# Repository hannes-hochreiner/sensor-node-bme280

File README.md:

# Sensor node BME280

A breakout board for the sensor node core featuring the BME280.

## Main parts

### BME280
  * Bosch Sensortec: BME280
  * Digi-Key: [828-1063-1-ND](https://www.digikey.de/product-detail/en/bosch-sensortec/BME280/828-1063-1-ND/6136314)
  * [Datasheet](https://ae-bst.resource.bosch.com/media/_tech/media/datasheets/BST-BME280-DS002.pdf)
  * [Driver](https://github.com/BoschSensortec/BME280_driver)
  * Price: 6.61

### Connector
  * Sullins Connector Solutions: GRPB052VWVN-RC
  * Digi-Key: [S9015E-05-ND](https://www.digikey.de/product-detail/en/sullins-connector-solutions/GRPB052VWVN-RC/S9015E-05-ND/1786455)
  * [Datasheet](https://media.digikey.com/pdf/Data%20Sheets/Sullins%20PDFs/GRPB_%20_2VWVN-RC%2010954-C.pdf)
  * Price: 0.63

## Price

estimate: 10 EUR

## Size

11 mm x 13 mm (connector 2.25 mm in)

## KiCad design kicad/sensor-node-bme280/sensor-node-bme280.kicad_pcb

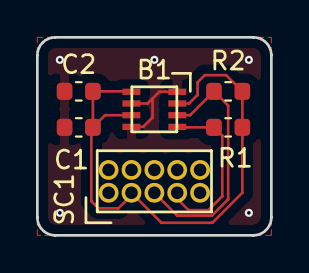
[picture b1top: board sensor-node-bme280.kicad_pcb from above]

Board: 2 copper layers, 13.0 x 11.0 mm, 6 parts (0 on the bottom side), 4 nets.

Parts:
B1: BME280; BME280_handsolder
C1, C2: 0.1µF; C_0603_1608Metric
R1, R2: 10k; R_0603_1608Metric
SC1: Sensor-Connector; sensor-connector-male

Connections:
/3V3: B1.2, B1.6, B1.8, C1.2, C2.2, R1.2, R2.2, SC1.3
/SCL: B1.4, R1.1, SC1.7
/SDA: B1.3, R2.1, SC1.5
GND: B1.1, B1.5, B1.7, C1.1, C2.1, SC1.1

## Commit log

2018-11-30 added layout
2018-12-01 added a kicad rendering of the board
2018-12-02 updated pin direction
2018-12-16 updated datasheet link
2018-12-16 added link to driver
2019-01-27 added pictures
